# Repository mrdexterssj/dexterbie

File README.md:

# Dexterbie

Dexterbie is a small tamagotchi-like device! It gives you a friend that sits in your desk during long coding hours. It has 2 buttons, the left one opens the menu and the right one opens the stats menu. It comes with a motion sensor and an environmental sensor, so you can interact physically with your virtual friend!

# What it is

Dexterbie is designed to just sit on your desk and do silly stuff to keep you company. You can interact with it in many ways: by tilting it or through the 2 built-in buttons!

The board includes a microcontroller, display, motion sensor and environmental sensor in a PCB design that looks like a flask. It's USB powered.

This project was created for week one of Hack Club's [Half Life Challenge](https://halflife.hackclub.com/) as an adaptation of [Starbie](https://github.com/SharKingStudios/Starbie), the official starter project.

# Project status

This project includes the 3D Models, Imported Parts.prety and kicad_mod files provided by the example as The Care Package. It also contains the base /Firmware from the tutorial, but with sprite modifications. It also contains JOURNAL.md and BOM.md which are auto-generated by Half Life internal systems. 

Inside /dexterbie you can find the kicad project directory, containing the schematic, PCB layout and other files.

# BOM Table

|Item            |QTY     |Price (w/o shipping or tax)|Description                  |Store page                                                                                                                                                                                                                                          |Note                               |
|----------------|--------|---------------------------|-----------------------------|----------------------------------------------------------------------------------------------------------------------------------------------------------------------------------------------------------------------------------------------------|-----------------------------------|
|XIAO ESP32-C3   |1       |13.63                      |Chipset to handle logic      |https://www.seeedstudio.com/Seeed-XIAO-ESP32C3-p-5431.html                                                                                                                                                                                          |                                   |
|0.96 OLED Screen|1       |2.43                       |The main display             |https://www.temu.com/ec/1-2-piezas-0-96-pulgadas---spi-puerto-serial-128x64-oled-driver--lcd--fuente-color---g-605515828562986.html                                                                                                                 |                                   |
|MPU6050         |1       |5.9                        |Sensor to detect movement    |https://www.temu.com/ec/-de-sensor-gy-521-mpu6050-de-2-piezas-interfaz-digital-iic-i2c-convertidor-ad-de-16-bits--de--de--para-proyectos-electronicos-diy-con-microcontrolador-g-605971430644580.html                                               |                                   |
|MX Switches     |1 (pack)|1.56                       |Key functionality            |https://www.temu.com/ec/kit-de-repuesto-de-interruptores-de-do-mecanico--para-reemplazar-piezas-danadas-de-interruptores-de-do-mecanico-desmontables-una-herramienta-para-tocar--que-se--a-las-necesidades-de-diferentes--de--g-605501937006272.html|                                   |
|10k resistor    |1 (pack)|2.82                       |Pull up mode resistor        |https://www.temu.com/ec/paquete-de-100-resistencias-de-pelicula-de-carbono-de-1-4-watt-con-un--de-tolerancia--disponibles-en--de-10--100--1k--y-10k--adecuadas-para-circuitos-electronicos-y--de-circuitos--sin-bateria-g-601102621590631.html      |Covered by me                      |
|DHT11           |1       |2.75                       |Environmental sensor         |https://www.mercadolibre.com.ec/dht11-sensor-de-temperatura-humedad-dht-11-arduino/p/MEC32624358                                                                                                                                                    |Covered by me                      |
|PCB             |1       |8.5                        |The body that holds the parts|https://www.jlcpcb.com/                                                                                                                                                                                                                             |Shipping (approx $35) covered by me|
|Keycaps         |1       |3.55                       |Make the switches usable     |https://www.temu.com/ec/juego-de-teclas-pbt-de-68-teclas-con---y--oem-de-tinte-sublimado-teclas-de-repuesto-minimalistas-de----con-teclado-mecanico-de-60-y-68-con-interruptores-mx-teclado-no-incluido-g-607600884198793.html                      |Covered by me                      |
|                |        |                           |                             |                                                                                                                                                                                                                                                    |                                   |
|Total (each kit)|1       |41                         |14                           |                                                                                                                                                                                                                                                    |                                   |

# Note
Some of the products aren't listed in the Parts List of the website, that's because the shipping costs are too high, or because I have easy access to them in physical stores:
* PCB: Shipping costs a lot (approx. $35), so I'll pay for it by myself
* DHT11: I have a physical store where I can buy it
* Resistors: I have a physical store where I can buy them
## Why is there no Tax & Shipping cost listed in the website?
Temu offers free shipping to my address, and taxes aren't significant unless customs requires extra payments

# Links

* Lapse 1: https://lapse.hackclub.com/timelapse/XROP2Fo1KQ4o
* Lapse 2: https://lapse.hackclub.com/timelapse/xe5cPkiZCGmo
* Lapse 3: https://lapse.hackclub.com/timelapse/F-Lf61B5Ms0S
* For more, check JOURNAL.md

# Screenshots

PCB editor overview

Front render

Back render

Schematic preview

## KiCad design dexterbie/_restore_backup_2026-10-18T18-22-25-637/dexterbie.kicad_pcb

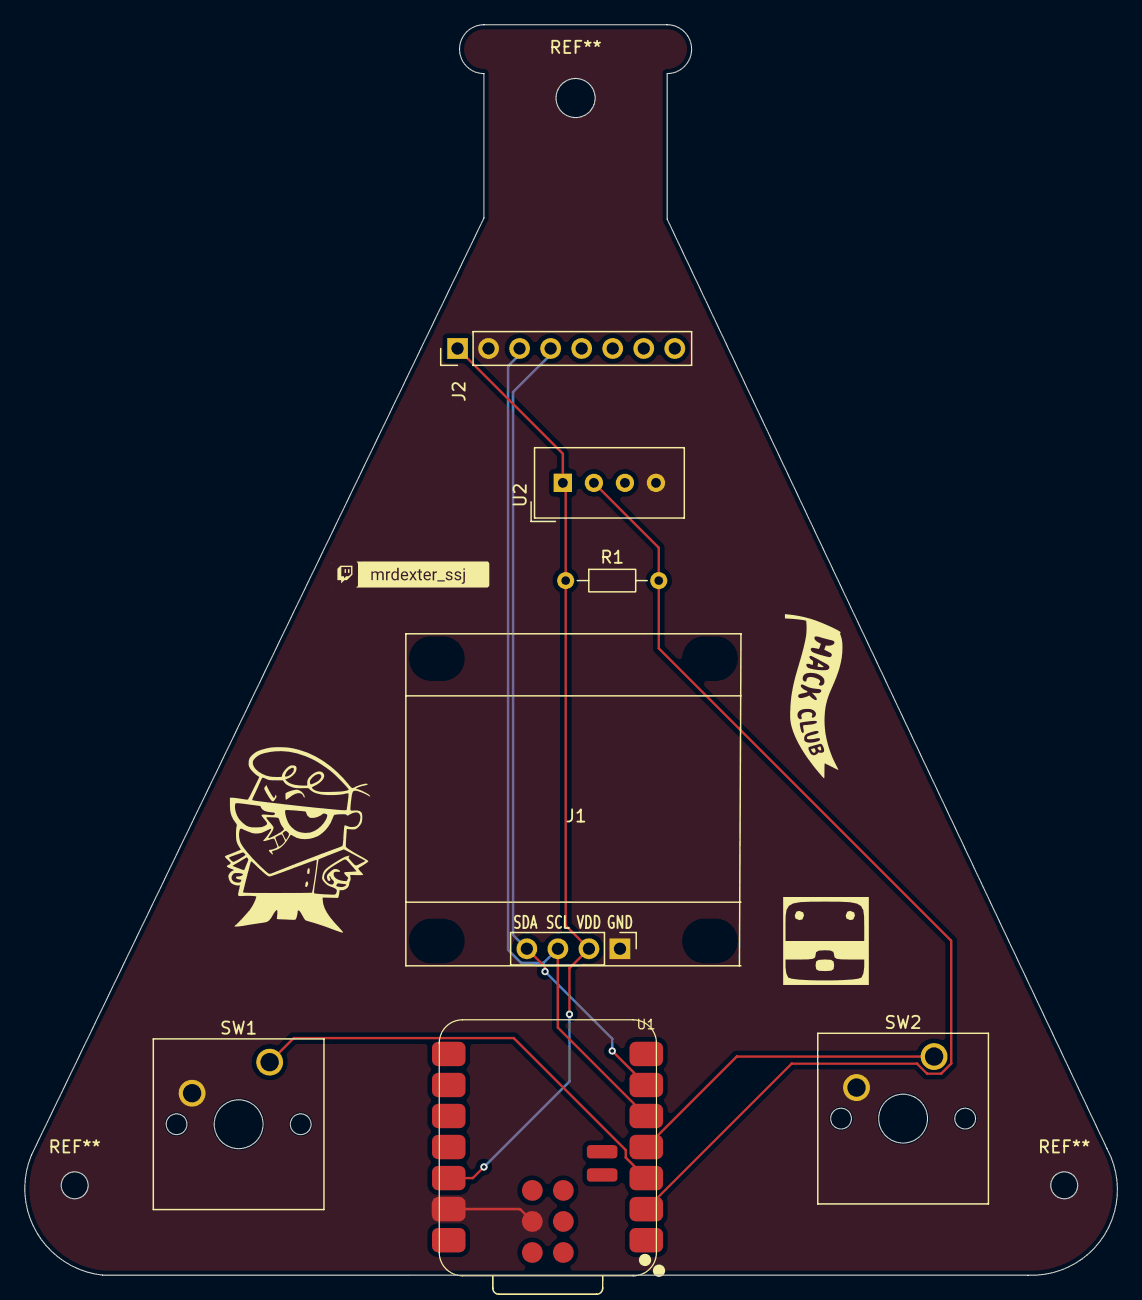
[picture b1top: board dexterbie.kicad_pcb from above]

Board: 2 copper layers, 89.4 x 102.3 mm, 7 parts (0 on the bottom side), 7 nets.

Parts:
J1: Conn_01x04_Pin; Display_128x64_096_I2C
J2: Conn_01x08_Pin; PinHeader_1x08_P2.54mm_Vertical
R1: 10k; R_Axial_DIN0204_L3.6mm_D1.6mm_P7.62mm_Horizontal
SW1, SW2: SW_Push; SW_Cherry_MX_1.00u_PCB
U1: XIAO-ESP32-C3-SMD
U2: DHT11; Aosong_DHT11_5.5x12.0_P2.54mm

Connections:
+3.3V: J1.2, J2.1, R1.1, U1.12 (3V3_OUT), U2.1 (VDD)
/DHT11 DATA: R1.2, U1.2 (D1), U2.2 (DATA)
/GPIO2: SW1.1, U1.3 (D2)
/GPIO3: SW2.1, U1.4 (D3)
/SCL: J1.3, J2.3, U1.5 (D4)
/SDA: J1.4, J2.4, U1.6 (D5)
GND: J1.1, J2.2, SW1.2, SW2.2, U1.13 (GND), U1.18 (GND), U2.4 (GND)
